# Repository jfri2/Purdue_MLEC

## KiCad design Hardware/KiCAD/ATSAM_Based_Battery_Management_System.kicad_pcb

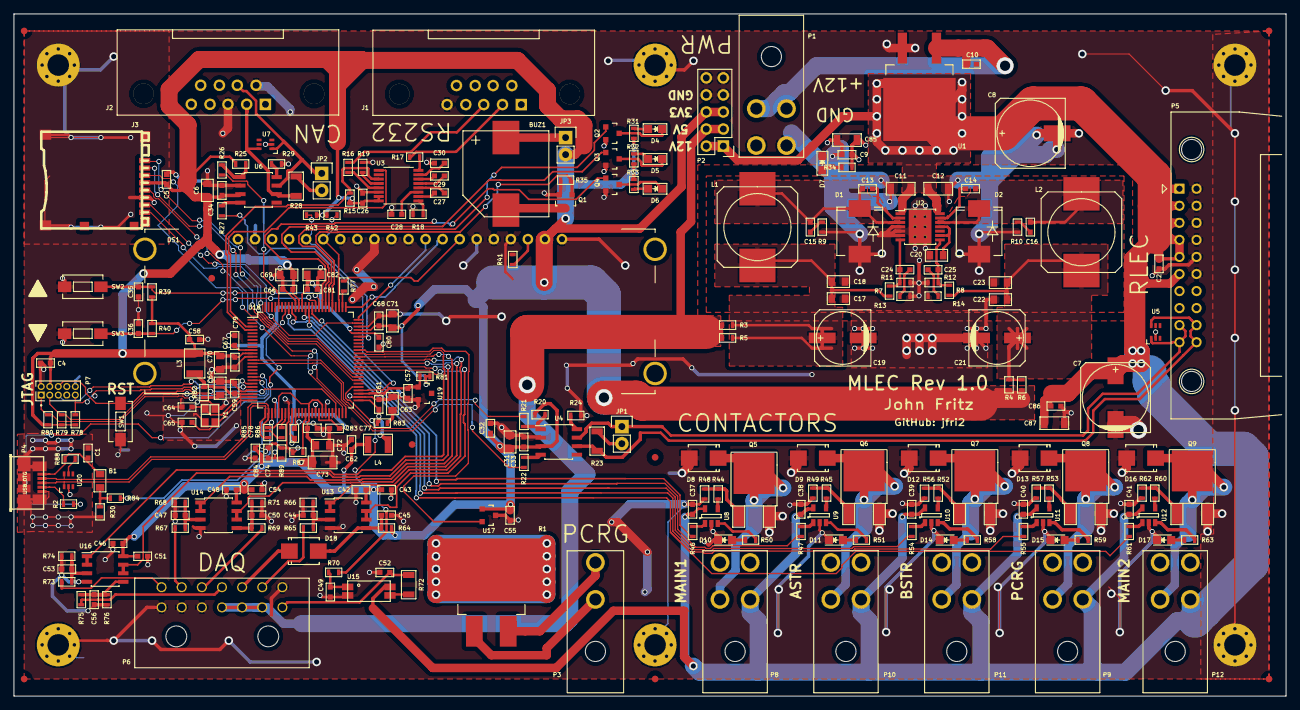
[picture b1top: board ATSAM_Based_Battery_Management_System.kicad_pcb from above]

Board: 2 copper layers, 189.5 x 101.6 mm, 259 parts (0 on the bottom side), 161 nets.

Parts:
B1: Ferrite Bead; C_0805_OUTLINE
BUZ1: BUZZER; SMI-1324-TW-3V-R
C1, C24: 10nF; C_0603_OUTLINE
C2, C4, C5, C9, C10, C26, C27, C28, C29, C30, C32, C34, C35, C36, C37, C38, C39, C40, C41, C42, C43, C44, C45, C46, C47, C48, C49, C50, C51, C52, C53, C54, C55, C56, C57, C58, C59, C61, C62, C66, C67, C68, C77, C78, C79, C80, C81, C83, C84, C86: 100nF; C_0603_OUTLINE
C6, C17, C18, C22, C23, C31: 10uF; C_0805_OUTLINE
C7, C8: 470uF; c_elec_10x10.5
C11, C12, C85, C87: 10uF; C_1206_OUTLINE
C13, C14: 33nF; C_0603_OUTLINE
C15, C16: 470pF; C_0603_OUTLINE
C19, C21: 100uF; c_elec_8x6.5
C20, C60, C63, C69, C70, C71, C72, C82: 4.7uF; C_0805_OUTLINE
C25: 6.8nF; C_0603_OUTLINE
C33: 10uF; C_0603_OUTLINE
C64, C65: 22pF; C_0603_OUTLINE
C73: 22uF; C_1206_OUTLINE
C74: 10pF; C_0603_OUTLINE
D1, D2: MBRS320TR; SMC_Standard
D4: ULED1; LED_0805_OUTLINE
D5: ULED2; LED_0805_OUTLINE
D6: ULED3; LED_0805_OUTLINE
D7: Power; LED_0805_OUTLINE
D8, D9, D12, D13, D16, D18: SS26; SMB_Standard
D10: MAIN1; LED_0805
D11: ASTR; LED_0805
D14: BSTR; LED_0805
D15: PCRG; LED_0805
D17: MAIN2; LED_0805
DS1: NHD-0216CW; NHD_OLED_2x16
FI1, FI2, FI3, FI4, FI5, FI6, FI7, FI8: Fiducal; Fiducial_1mm_Dia_2.54mm_Outer_CopperTop
J1: RS232_0; Assmann_DB9_ADX09
J2: VEHICLE_CAN; Assmann_DB9_ADX09
J3: microSD_Card; microsd_socket
JP1, JP2, JP3: JUMPER; Pin_Header_Straight_1x02
L1, L2: 22uH; SELF-WE-PD-XXL
L3, L4: 10uH; C_1210_OUTLINE
P1: 12V_CONN; MiniFit_Angled-4
P2: PWR_JP; Pin_Header_Straight_2x05
P3: PCRG; MiniFit_Angled-2
P4: USB_OTG; conn_usb_B_micro_smd
P5: RLEC; 3M_RightAngle_20pos_N3428-5202RB
P6: MLEC_DAQ_CONN; Molex_Microfit3_Header_02x07_Angled_43045-140x
P7: JTAG; Pin_Header_Straight_2x05_Pitch1.27mm
P8: MAIN_1_CONT; MiniFit_Angled-4
P9: PCRG_CONT; MiniFit_Angled-4
P10: ASTR_CONT; MiniFit_Angled-4
P11: BSTR_CONT; MiniFit_Angled-4
P12: MAIN_2_CONT; MiniFit_Angled-4
Q1, Q2, Q3, Q4: BSS214N; SOT-23
Q5, Q6, Q7, Q8, Q9: AOD516; TO-252-2Lead
R1: 100; D2PAK-2Lead-7106DG_Heatsink
R2, R3, R4, R5, R6, R16, R17, R18, R19, R21, R22, R26, R27, R41, R44, R45, R52, R53, R60: 0R; R_0603_OUTLINE
R7, R8, R30: 20k; R_0603_OUTLINE
R9, R10: 10; R_0603_OUTLINE
R11: 3.83k; R_0603_OUTLINE
R12: 6.34k; R_0603_OUTLINE
R13: 422; R_0603_OUTLINE
R14: 698; R_0603_OUTLINE
R15, R20, R24, R25, R29, R35, R39, R40, R42, R43, R48, R49, R56, R57, R62, R84, R88: 10k; R_0603_OUTLINE
R23, R28: 120; R_1206_OUTLINE
R31, R32, R33: 470; R_0603_OUTLINE
R34, R46, R47, R50, R51, R54, R55, R58, R59, R61, R63, R64, R66, R71, R76, R87: 1k; R_0603_OUTLINE
R65, R69, R75: 19k; R_0603_OUTLINE
R67, R73: 3.3k; R_0603_OUTLINE
R68, R74: 5k; R_0603_OUTLINE
R70: 100; R_0603_OUTLINE
R72: 360; R_1206_OUTLINE
R77, R85, R86: 39; R_0603_OUTLINE
R78, R79, R80: 100k; R_0603_OUTLINE
R81: 4.7k; R_0603_OUTLINE
R82, R83: 1R; R_0603_OUTLINE
R89: 6.8k; R_0603_OUTLINE
SW1: SW_RST; SW_SPST_EVQPE1
SW2: OLED_UP_BUTTON; SW_SPST_EVQPE1
SW3: OLED_DOWN_BUTTON; SW_SPST_EVQPE1
U1: RBO40-40G; TO-263-2Lead
U2: TPS54383; HTSSOP-14_4.4x5mm_Pitch0.65mm
U3: ICL3221E; TSSOP-16_4.4x5mm_Pitch0.65mm
U4, U6: SN65HVD230; SOIC-8_3.9x4.9mm_Pitch1.27mm
U5, U7, U20: NUP2202; SC-70-6
U8, U9, U10, U11, U12: IRS44273L; SOT-23-5
U13, U14, U16: MCP6002; SOIC-8_3.9x4.9mm_Pitch1.27mm
U15: PC3H71x; PC3H710
U17: MCP9700-TT; SOT-23
U18: SAM3X4/8C-100LQFP; LQFP-100_14x14mm_Pitch0.5mm
U19: LM4040; SOT-23
W1, W2, W3, W4, W5, W6: GND; MountingHole_3.2mm_M3_Pad_Via
Y1: 12MHz; crystal_FA238-TSX3225

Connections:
+5V: P2.3, P2.4, P6.2, P6.3, P6.4, R3.2, R5.2
+12V: C2.2, C7.1, C8.1, C9.1, C11.1, C12.2, C37.1, C38.1, C39.1, C40.1, C41.1, C85.2, C86.1, C87.2, P2.1, P2.2, P5.1, P5.3, P5.5, P5.7, P5.9, P5.11, P8.1, P9.1, P10.1, P11.1, P12.1, R34.1, U1.3, U2.1, U2.14, U8.5, U9.5, U10.5, U11.5, U12.5, U15.4
/CAN/RLEC_CAN+: JP1.1, P5.17, P5.19, U4.7, U5.1
/CAN/RLEC_CAN-: P5.18, P5.20, R23.2, U4.6, U5.6
/CAN/VEHICLE_CAN+: J2.7, JP2.1, U6.7, U7.1
/CAN/VEHICLE_CAN-: J2.2, R28.2, U6.6, U7.6
/Contact_Drivers/ASTR_CONT_LOGIC: R47.2, U18.88
/Contact_Drivers/ASTR_CONT_LOGIC_SINK: D9.1, P10.2, Q6.2
/Contact_Drivers/BSTR_CONT_COIL_SINK: D12.1, P11.2, Q7.2
/Contact_Drivers/BSTR_CONT_LOGIC: R54.2, U18.92
/Contact_Drivers/MAIN_1_CONT_LOGIC: R46.2, U18.86
/Contact_Drivers/MAIN_2_CONT_LOGIC: R61.2, U18.93
/Contact_Drivers/MAIN_CONT_1_COIL_SINK: D8.1, P8.2, Q5.2
/Contact_Drivers/MAIN_CONT_2_COIL_SINK: D16.1, P12.2, Q9.2
/Contact_Drivers/PCRG_CONT_COIL_SINK: D13.1, P9.2, Q8.2
/DAQ/ASTR_2_ANALOG: P6.12, R69.1
/DAQ/ASTR_I_RATIO: P6.13, R67.1
/DAQ/BSTR_2_ANALOG: P6.11, R75.1
/DAQ/BSTR_I_RATIO: P6.14, R73.1
/DAQ/INJECT_12V_ISO: C52.1, P6.1, R72.1
/DAQ/INJECT_LOGIC: R70.2, U18.55
/DAQ/LOWSIDE_ANALOG: D18.1, P6.10
/DAQ/MAIN1_2_ANALOG: P6.9, R65.1
/Interface/BUZZ_GATE_DRIVE: Q1.1, R35.1, U18.80
/Interface/OLED_DOWN: C36.1, R40.1, SW3.1, U18.85
/Interface/OLED_SCK: DS1.7, R77.1
/Interface/OLED_SDI: DS1.8, U18.76
/Interface/OLED_SDO: DS1.9, U18.75
/Interface/OLED_UP: C35.1, R39.1, SW2.1, U18.84
/Interface/~OLED_CS: DS1.15, R42.1, U18.78
/Interface/~OLED_RST: DS1.16, R43.2, U18.70
/MCU/ADC_0: U13.1, U13.2, U18.63
/MCU/ADC_1: U14.6, U14.7, U18.62
/MCU/ADC_2: U16.6, U16.7, U18.61
/MCU/ADC_3: U13.6, U13.7, U18.60
/MCU/ADC_8: U14.1, U14.2, U18.64
/MCU/ADC_9: U16.1, U16.2, U18.65
/MCU/ADC_10: U17.2, U18.66
/MCU/ADVREF: C57.1, R81.2, U18.53, U19.1
/MCU/CAN0_RX: R22.2, U18.14
/MCU/CAN0_TX: R21.2, U18.13
/MCU/CAN1_RX: R27.2, U18.54
/MCU/CAN1_TX: R26.2, U18.96
/MCU/MCCDA: J3.3, U18.50
/MCU/MCCK: J3.5, U18.49
/MCU/MCDA0: J3.7, U18.74
/MCU/MCDA1: J3.8, U18.59
/MCU/MCDA2: J3.1, U18.58
/MCU/MCDA3: J3.2, U18.57
/MCU/MCU_DFSD+: R85.1, U18.31
/MCU/MCU_DFSD-: R86.1, U18.32
/MCU/PB1: Q2.1, U18.81
/MCU/PB2: Q3.1, U18.82
/MCU/PB3: Q4.1, U18.83
/MCU/PB7: R55.2, U18.87
/MCU/TCK: P7.1, R80.1, U18.18
/MCU/TDI: P7.3, R79.1, U18.19
/MCU/TDO: P7.5, U18.20
/MCU/TMS: P7.9, R78.1, U18.21
/MCU/UART0_RX: U3.9, U18.3
/MCU/UART0_TX: R15.1, U3.11, U18.4
/MCU/UOTGID: R2.1, U18.94
/MCU/USBD+: P4.3, R85.2, U18.26, U20.1
/MCU/USBD-: P4.2, R86.2, U18.27, U20.6
/MCU/VBUS: B1.2, C1.1, P4.1, R88.1
/MCU/~NRST: P7.6, SW1.1, U18.47
/Power_Supply/3V3_OUT: C21.1, C22.1, C23.1, L2.2, R4.1, R6.1, R8.1
/Power_Supply/5V_OUT: C17.1, C18.1, C19.1, L1.2, R3.1, R5.1, R7.1
/Power_Supply/FB_5: C24.1, R7.2, R11.1, U2.7
/Power_Supply/FB_33: C25.1, R8.2, R12.1, U2.8
/Power_Supply/SW_5: C13.2, C15.1, D1.1, L1.1, U2.3
/Power_Supply/SW_33: C14.2, C16.1, D2.1, L2.1, U2.12
/Power_Supply/VIN: C10.1, P1.1, P1.2, U1.1
/RS232/RS232_FORCEON: R19.1, U3.12
/RS232/RS232_RX: J1.2, R17.1
/RS232/RS232_TX: J1.3, R16.1
/RS232/RS232_~EN: R18.1, U3.1
/UOTGID_U: P4.4, R2.2
GND: C1.2, C2.1, C4.2, C5.2, C6.2, C7.2, C8.2, C9.2, C10.2, C11.2, C12.1, C17.2, C18.2, C19.2, C20.2, C21.2, C22.2, C23.2, C26.1, C28.2, C30.2, C31.2, C32.2, C33.2, C34.2, C35.2, C36.2, C37.2, C38.2, C39.2, C40.2, C41.2, C42.1, C43.1, C44.2, C45.2, C46.1, C47.2, C48.1, C49.2, C50.2, C51.1, C52.2, C53.2, C54.1, C55.1, C56.2, C57.2, C58.2, C59.2, C60.2, C61.2, C62.2, C63.2, C64.2, C65.2, C66.2, C67.2, C68.2, C69.2, C70.2, C71.2, C72.2, C73.2, C74.2, C77.2, C78.2, C79.2, C80.2, C81.2, C82.2, C83.2, C84.2, C85.1, C86.2, C87.1, D1.2, D2.2, D7.1, D8.2, D9.2, D10.1, D11.1, D12.2, D13.2, D14.1, D15.1, D16.2, D17.1, DS1.1, DS1.4, DS1.5, DS1.6, DS1.10, DS1.11, DS1.12, DS1.13, DS1.14, DS1.17, DS1.18, DS1.19, DS1.20, J1.5, J2.3, J2.6, J3.6, J3.9, P1.3, P1.4, P2.7, P2.8, P2.9, P2.10, P4.5, P4.6, P5.2, P5.4, P5.6, P5.8, P5.10, P5.12, P6.5, P6.6, P6.7, P6.8, P7.2, P7.10, Q1.2, Q2.2, Q3.2, Q4.2, Q5.3, Q6.3, Q7.3, Q8.3, Q9.3, R9.2, R10.2, R11.2, R12.2, R13.2, R14.2, R18.2, R19.2, R24.2, R29.2, R30.2, R35.2, R41.2, R48.2, R49.2, R56.2, R57.2, R62.2, R66.2, R68.2, R71.2, R74.2, R76.2, R87.2, R89.2, SW1.2, SW2.2, SW3.2, U1.2, U2.4, U2.5, U2.6, U2.15, U3.14, U4.2, U5.2, U6.2, U7.2, U8.2, U9.2, U10.2, U11.2, U12.2, U13.4, U14.4, U15.2, U16.4, U17.3, U18.12, U18.22, U18.33, U18.35, U18.41, U18.44, U18.52, U18.73, U18.91, U19.2, U20.2, W1.1, W2.1, W3.1, W4.1, W5.1, W6.1, Y1.3
unnamed: B1.1, R30.1, R84.2
unnamed: BUZ1.1, Q1.3
unnamed: BUZ1.2, JP3.1
unnamed: C13.1, U2.2
unnamed: C14.1, U2.13
unnamed: C15.2, R9.1
unnamed: C16.2, R10.1
unnamed: C20.1, U2.9, U2.11
unnamed: C24.2, R13.1
unnamed: C25.2, R14.1
unnamed: C27.1, U3.4
unnamed: C27.2, U3.2
unnamed: C28.1, U3.3
unnamed: C29.1, U3.6
unnamed: C29.2, U3.5
unnamed: C30.1, U3.7
unnamed: C44.1, R65.2, R66.1, U13.3
unnamed: C45.1, D18.2, R64.2, U13.5
unnamed: C47.1, R67.2, R68.1, U14.3
unnamed: C49.1, R70.1, U15.1
unnamed: C50.1, R69.2, R71.1, U14.5
unnamed: C53.1, R73.2, R74.1, U16.3
unnamed: C56.1, R75.2, R76.1, U16.5
unnamed: C59.1, L3.1, R82.1, U18.23
unnamed: C60.1, R82.2
unnamed: C61.1, L4.1, R83.1, U18.51
unnamed: C63.1, R83.2
unnamed: C64.1, U18.24, Y1.1
unnamed: C65.1, U18.25, Y1.2
unnamed: C74.1, R89.1, U18.29
unnamed: D4.1, Q2.3
unnamed: D4.2, R31.2
unnamed: D5.1, Q3.3
unnamed: D5.2, R32.2
unnamed: D6.1, Q4.3
unnamed: D6.2, R33.2
unnamed: D7.2, R34.2
unnamed: D10.2, R50.2
unnamed: D11.2, R51.2
unnamed: D14.2, R58.2
unnamed: D15.2, R59.2
unnamed: D17.2, R63.2
unnamed: DS1.3, R41.1
unnamed: JP1.2, R23.1
unnamed: JP2.2, R28.1
unnamed: P3.1, R1.1
unnamed: P3.2, R1.2
unnamed: Q5.1, R44.1, R48.1
unnamed: Q6.1, R45.1, R49.1
unnamed: Q7.1, R52.1, R56.1
unnamed: Q8.1, R53.1, R57.1
unnamed: Q9.1, R60.1, R62.1
unnamed: R16.2, U3.13
unnamed: R17.2, U3.8
unnamed: R20.2, R21.1, U4.1
unnamed: R22.1, U4.4
unnamed: R24.1, U4.8
unnamed: R25.2, R26.1, U6.1
unnamed: R27.1, U6.4
unnamed: R29.1, U6.8
unnamed: R44.2, U8.4
unnamed: R45.2, U9.4
unnamed: R46.1, U8.1
unnamed: R47.1, U9.1
unnamed: R50.1, U8.3
unnamed: R51.1, U9.3
unnamed: R52.2, U10.4
unnamed: R53.2, U11.4
unnamed: R54.1, U10.1
unnamed: R55.1, U11.1
unnamed: R58.1, U10.3
unnamed: R59.1, U11.3
unnamed: R60.2, U12.4
unnamed: R61.1, U12.1
unnamed: R63.1, U12.3
unnamed: R72.2, U15.3
unnamed: R77.2, U18.77
unnamed: R84.1, U18.28
unnamed: R87.1, U18.38
unnamed: R88.2, U20.5
VDDBU: C4.1, C5.1, C6.1, C26.2, C31.1, C32.1, C33.1, C34.1, C42.2, C43.2, C46.2, C48.2, C51.2, C54.2, C55.2, C58.1, C62.1, C66.1, C67.1, C68.1, C69.1, C70.1, C71.1, C72.1, C73.1, C83.1, C84.1, DS1.2, J3.4, JP3.2, L3.2, L4.2, P2.5, P2.6, P7.4, R4.2, R6.2, R15.2, R20.1, R25.1, R31.1, R32.1, R33.1, R39.2, R40.2, R42.2, R43.1, R64.1, R78.2, R79.2, R80.2, R81.1, U3.15, U3.16, U4.3, U6.3, U13.8, U14.8, U16.8, U17.1, U18.11, U18.30, U18.39, U18.43, U18.72, U18.90
VDDCORE: C77.1, C78.1, C79.1, C80.1, C81.1, C82.1, U18.10, U18.34, U18.42, U18.45, U18.71, U18.89

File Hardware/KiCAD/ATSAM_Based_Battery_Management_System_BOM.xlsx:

| Title | MLEC
 | Revision | 1
 | Date | 42472
 | Generated | 42478.914085648146
 | Company | Purdue University
 | Designer | John Fritz
 | Total Parts | 246
 | Total Unique Parts | 71
 |  |  | Reference | Qty (1 board theory) | Qty (1 board actual) | Qty (2 board actual) | Value | Tolerance | Footprint | Mfg# | DigiKey# | Comments
 |  |  | B1 | 1 | 2 | 5 | 600R Ferrite Bead |  | 0805 | MI0805K601R-10 | 240-2390-1-ND
 |  |  | BUZ1 | 1 | 1 | 2 | BUZZER |  | Custom | SMI-1324-TW-3V-R | 668-1386-5-ND
 |  |  | C2 C4 C5 C10 C9 C86 C26 C27 C29 C28 C30 C32 C34 C35 C36 C41 C40 C39 C37 C38 C48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 | 51 | 100 | 150 | 100nF | 0.2 | 0603 | C0603C104M5RACTU | 399-7845-1-ND
 |  |  | C1 C24 | 2 | 4 | 10 | 10nF | 0.01 | 0603 | C0603C102F5GACTU | 399-7826-1-ND
 |  |  | C6 C31 C22 C23 C18 C17 | 6 | 8 | 20 | 10uF | 0.2 | 0805 | C0805C106K8RACTU | 490-1718-1-ND
 |  |  | C8 C7 | 2 | 3 | 5 | 470uF | 0.2 | SMD 10mm Dia | UCL1V471MNL1GS | 493-3961-1-ND
 |  |  | C20 C63 C71 C60 C72 C82 C70 C69 | 8 | 10 | 20 | 4.7uF | 0.1 | 0805 | C1206C475K3RACTU | 399-8204-1-ND
 |  |  | C14 C13 | 2 | 4 | 10 | 33nF | 0.1 | 0603 | C0603C333K3RACTU | 399-7904-1-ND
 |  |  | C11 C12 C85 C87 | 4 | 6 | 10 | 10uF | 0.1 | 1206 | C1206C106K3RACTU | 399-7442-1-ND
 |  |  | C21 C19 | 2 | 3 | 4 | 100uF | 0.2 | SMD 8mm Dia | EEEFC1A101P | PCE3989CT-ND
 |  |  | C25 | 1 | 3 | 10 | 6.8nF | 0.01 | 0603 | C0603C682F3GACTU | 399-11154-1-ND
 |  |  | C16 C15 | 2 | 4 | 10 | 470pF | 0.01 | 0603 | C1608C0G1H471F080AA | 445-5370-1-ND
 |  |  | C73 | 1 | 2 | 10 | 22uF |  | 1206 | C1206C226M8RACTU | 399-7444-1-ND
 |  |  | C64 C65 | 2 | 4 | 10 | 22pF | 0.01 | 0603 | C0603C220F1GACTU | 399-11145-1-ND
 |  |  | C74 | 1 | 2 | 10 | 10pF | 0.01 | 0603 | C0603C100F5GAC7867 | 399-9958-1-ND
 |  |  | D2 D1 | 2 | 3 | 4 | MBRS320TR |  | SMC | MBRS320 | MBRS320CT-ND
 |  |  | D7 | 1 | 2 | 10 | Power | Green | 0805 | HSMG-C170 | 516-1434-1-ND
 |  |  | D16 D13 D12 D8 D9 D18 | 6 | 8 | 20 | SS26 |  | SMB | SS26 | SS26FSCT-ND
 |  |  | D4 D5 D6 D10 D11 D14 D15 D17 | 8 | 10 | 20 | General LED | Amber | 0805 | HSMA-C170 | 516-1431-1-ND
 |  |  | DS1 | 1 | 1 | 2 | NHD-0216CW |  | Custom | NHD-0216CW-AB3 | NHD-0216CW-AB3-ND | If OLED is unused, DS1 can be left unpopulated
 |  |  | J1 | 1 | 1 | 2 | RS232_0 |  | DB9 Female | A-DF 09 A/KG-T4S | AE10924-ND | Alternate part: ADS09A-KG-TAXB5
 |  |  | J2 | 1 | 1 | 2 | VEHICLE_CAN |  | DB9 Male | A-DS 09 A/KG-T4S | AE10970-ND | Alternate part: ADF09A-KG-TASB5
 |  |  | J3 | 1 | 1 | 2 | microSD_Card |  | Custom microSD | 5027740891 | WM24066CT-ND
 |  |  | JPX | 1 | 1 | 2 | Breakaway Pin headers |  | Pin Header | PEC36SAAN | S1012E-36-ND
 |  |  | SHX | 3 | 3 | 10 | Jumper Shunts |  |  | 969102-0000-DA | 3M9580-ND
 |  |  | L2 L1 | 2 | 2 | 5 | 22uH |  | 12.5mm x 12.5mm | DRA127-220-R | 283-3590-1-ND
 |  |  | L4 L3 | 2 | 2 | 5 | 10uH |  | 1210 | CBC3225T100MR | 587-1625-1-ND
 |  |  | P8 P9 P10 P11 P12 P1 | 6 | 6 | 14 | 2x2 Connectors |  | Molex MiniFit jr 2x2 | 39301042 | WM21364-ND
 |  |  | P5 | 1 | 1 | 2 | RLEC |  | 20pos 3M Shrouded | N3428-5202RB | MHR20S-ND
 |  |  | P7 | 1 | 1 | 3 | JTAG |  | 10pos 1.27mm | 62201021121 | 732-5374-ND
 |  |  | P4 | 1 | 1 | 3 | USB_OTG |  | USB Micro-B | 10118192-0001LF | 609-4613-1-ND
 |  |  | P3 | 1 | 1 | 2 | PCRG |  | Molex MiniFit jr 1x2 | 39301022 | WM21363-ND
 |  |  | P6 | 1 | 1 | 2 | MLEC_DAQ_CONN |  | Molex MicroFit 2x7 | 430451401 | WM12758-ND
 |  |  | Q4 Q3 Q2 Q1 | 4 | 6 | 15 | BSS214N |  | SOT-23 | BSS214N H6327 | BSS214N H6327TR-ND | If Buzzer is unused Q1 can be left unpopulated
 |  |  | Q9 Q8 Q7 Q5 Q6 | 5 | 5 | 14 | AOD516 |  | DPAK | AOD516 | 785-1358-1-ND
 |  |  | HS1 | 1 | 1 | 3 | Heatsink |  | D2PAK | 7106DG | HS412-ND
 |  |  | R1 | 1 | 1 | 3 | 100 |  | D2PAK | PFS35-100RF1 | 696-1277-1-ND
 |  |  | R2 R6 R4 R5 R3 R18 R19 R16 R17 R21 R22 R26 R27 R41 R60 R53 R52 R44 R45 | 19 | 50 | 100 | 0R |  | 0603 | ERJ-3GEY0R00V | P0.0GCT-ND | If OLED is unused, R41 can be left unpopulated
 |  |  | R8 R7 R30 | 3 | 5 | 10 | 20k | 0.01 | 0603 | ERJ-3EKF2002V | P20.0KHCT-ND
 |  |  | R12 | 1 | 3 | 10 | 6.34k | 0.01 | 0603 | ERJ-3EKF6341V | P6.34KHCT-ND
 |  |  | R14 | 1 | 3 | 10 | 698 | 0.01 | 0603 | ERJ-3EKF6980V | P698HCT-ND
 |  |  | R10 R9 | 2 | 4 | 10 | 10 | 0.05 | 0603 | ERJ-PA3F10R0V | P10.00BYCT-ND
 |  |  | R11 | 1 | 3 | 10 | 3.83k | 0.01 | 0603 | ERJ-3EKF3831V | P3.83KHCT-ND
 |  |  | R13 | 1 | 3 | 10 | 422 | 0.01 | 0603 | ERJ-3EKF4220V | P422HCT-ND
 |  |  | R15 R20 R24 R25 R29 R35 R39 R40 R42 R43 R62 R57 R56 R48 R49 R84 R88 | 17 | 50 | 50 | 10k | 0.01 | 0603 | ERJ-3EKF1002V | P10.0KHCT-ND | If Buzzer is unused R35 can be left unpopulated. If OLED is unused, R42 and R43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
 |  |  | R23 R28 | 2 | 4 | 10 | 120 | 1% 1/8 Watt | 1206 | ERJ-8ENF1200V | P120FCT-ND
 |  |  | R34 R61 R63 R55 R59 R54 R58 R46 R50 R47 R51 R71 R76 R66 R64 R87 | 16 | 25 | 50 | 1k | 0.01 | 0603 | ERJ-3EKF1001V | P1.00KHCT-ND
 |  |  | R31 R32 R33 | 3 | 5 | 10 | 470 | 1/4 Watt | 0603 | ERJ-3EKF4700V | P470HCT-ND
 |  |  | R69 R75 R65 | 3 | 5 | 10 | 19k | 0.01 | 0603 | ERJ-3EKF1912V | P19.1KHCT-ND
 |  |  | R70 | 1 | 3 | 10 | 100 | 1/8 Watt | 0603 | ERJ-PA3F1000V | P100BYCT-ND
 |  |  | R72 | 1 | 3 | 10 | 360 | 1/2 Watt | 1206 | CRCW1206360RFKEAHP | 541-360UCT-ND
 |  |  | R67 R73 | 2 | 4 | 10 | 3.3k | 0.01 | 0603 | ERJ-3EKF3301V | P3.30KHCT-ND
 |  |  | R68 R74 | 2 | 4 | 10 | 5k | 0.01 | 0603 | ERJ-3EKF4991V | P4.99KHCT-ND
 |  |  | R81 | 1 | 3 | 10 | 4.7k |  | 0603 | ERJ-3EKF4701V | P4.70KHCT-ND
 |  |  | R83 R82 | 2 | 4 | 10 | 1 |  | 0603 | ERJ-3BQF1R0V | P17371CT-ND
 |  |  | R79 R80 R78 | 3 | 5 | 10 | 100k |  | 0603 | ERJ-3EKF1003V | P100KHCT-ND
 |  |  | R89 | 1 | 3 | 10 | 6.8k | 0.01 | 0603 | ERJ-3EKF6801V | P6.80KHCT-ND
 |  |  | R77 R85 R86 | 3 | 5 | 10 | 39 |  | 0603 | ERJ-6ENF39R0V | P39.0CCT-ND | If OLED is unused, R77 can be left unpopulated
 |  |  | SW1 SW2 SW3 | 3 | 5 | 10 | Pushbutton |  |  | EVQ-PE105K | P13594SCT-ND
 |  |  | U2 | 1 | 2 | 4 | TPS54383 |  | 14-HTSSOP | TPS54383PWP | 296-26995-5-ND
 |  |  | U1 | 1 | 2 | 4 | RBO40-40G |  | D2PAK | RBO40-40G-TR | 497-3714-1-ND
 |  |  | U3 | 1 | 2 | 4 | ICL3221E |  | 16-TSSOP | ICL3221EIVZ-T | ICL3221EIVZ-TCT-ND
 |  |  | U4 U6 | 2 | 3 | 6 | SN65HVD230 |  | 8-SOIC | SN65HVD230DR | 296-11654-1-ND
 |  |  | U5 U7 U20 | 3 | 5 | 10 | NUP2202 |  | 6-TSSOP | NUP2202W1T2G | NUP2202W1T2GOSCT-ND
 |  |  | U12 U11 U10 U8 U9 | 5 | 5 | 12 | IRS44273L |  | SOT-23-5 | IRS44273LTRPBF | IRS44273LTRPBFCT-ND
 |  |  | U14 U16 U13 | 3 | 5 | 8 | MCP6002 |  | 8-SOIC | MCP6002T-I/SN | MCP6002T-I/SNCT-ND
 |  |  | U17 | 1 | 3 | 5 | MCP9700-TT |  | SOT-23 | MCP9700T-E/TT | MCP9700T-E/TTCT-ND
 |  |  | U15 | 1 | 2 | 4 | PC3H71x |  | 4-SOIC | PC3H710NIP0F | 425-2108-1-ND
 |  |  | U18 | 1 | 2 | 3 | SAM3X4/8C-100LQFP |  | 100-LQFP | ATSAM3X8CA-AU | ATSAM3X8CA-AU-ND
 |  |  | U19 | 1 | 2 | 5 | LM4040 |  | SOT-23 | LM4040C30IDBZR | 296-20887-1-ND
 |  |  | Y1 | 1 | 2 | 4 | 12MHz |  | 4-SMD | FA-238V 12.0000MB-K3 | SER3682CT-ND
 |  |  | BOM made with KICAD_BOM_WIZARD (https://github.com/HashDefineElectronics/KiCad_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
 |  |  | Generated 4/18/2016 9:56:17 PM

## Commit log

2016-05-09 Initial Commit
    Hardware v1.0
    Software still in dev
2016-05-09 Added OLED functions
2016-05-21 Removed USB, and SPI. Fixed hard fault issue
    Never use pio_set_pin_high or pio_set_pin_low functions - was
    hardfaulting when those were active
2016-05-21 Removed zip files
